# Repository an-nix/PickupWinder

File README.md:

# PickupWinder — Raspberry Pi + ESP32 Automated Winding Controller

An automated guitar pickup winding system driven by a Raspberry Pi host and an ESP32 real-time motion controller. The RPi handles planning, geometry, and user-facing APIs. The ESP32 drives the stepper motors in hard real-time using the RMT peripheral.

---

## Table of contents

1. [What it does](#what-it-does)
2. [Hardware overview](#hardware-overview)
3. [Repository layout](#repository-layout)
4. [Key concepts](#key-concepts)
5. [Getting started](#getting-started)
6. [Configuration reference](#configuration-reference)
7. [Winding a pickup — step by step](#winding-a-pickup--step-by-step)
8. [JSON-RPC API quick reference](#json-rpc-api-quick-reference)
9. [Further reading](#further-reading)

---

## What it does

PickupWinder automates or semi-automates the process of winding guitar pickup coils.
The machine moves two stepper axes in synchrony:

- **Spindle axis (axis 0)**: rotates the pickup bobbin.
- **Lateral axis (axis 1)**: moves the wire guide back and forth across the winding window.

The host computes exactly how far the guide must travel for each spindle revolution
(the *layer pitch*) and streams that motion to the ESP32 as pre-computed multi-axis
segment blocks. The ESP32 expands those segments into step pulses and streams them
to the motor drivers via the RMT peripheral.

Two winding modes are supported:

| Mode | Class | Description |
|------|-------|-------------|
| **Classic** | `WindingEngine` | Fixed program: N turns, fixed window, optional scatter, one shot. |
| **Adaptive** | `AdaptiveWindingService` | Live session: target RPM, window, and pitch can be changed while running. Progress is tracked in turns. |

---

## Hardware overview

```
  Raspberry Pi                     ESP32
  ─────────────────────────────────────────────────────
  spidev (master, mode 1) ──SPI──> slave (mode 1, DMA)
  GPIO poll / sysfs       <──────  GPIO17 READY output
  (optional shutdown)     <──────  GPIO16 RPI_SHUTDOWN_REQ

  ESP32 ──STEP/DIR──> Spindle stepper driver ──> Bobbin
  ESP32 ──STEP/DIR──> Lateral stepper driver ──> Wire guide
  ESP32 <── HX711 (tension load cell)
  ESP32 <── Rotary encoder (optional spindle feedback)
  ESP32 <── Lateral endstop (2-contact homing sensor)
```

- SPI bus: fixed 512-byte frames, mode 1 (CPOL=0, CPHA=1), CRC16-CCITT-FALSE.
- The ESP32 signals that it is ready to accept a new frame by asserting GPIO17 (active high by default).
- Do **not** drive GPIO12 high at boot — it straps the ESP32 flash voltage.

---

## Repository layout

```
src/
  windy/              Python host application
    winding_main.py   Process entry point and signal handling
    app/runtime.py    Runtime composition (wires all components together)
    core/
      config.py       AppConfiguration dataclass — all machine parameters
      engine.py       WindingEngine — classic program execution
      lateral.py      Lateral homing, soft-limit enforcement
      command_service.py  Motion command building and queuing
      coordinator.py  Centralized stop/fault coordination
      shared_state.py Thread-safe state shared between engine and RPC
      events.py       EventBus (EventKind enum + async dispatch)
      status.py       Snapshot builders for RPC status responses
    motion/
      move_queue.py   Move serialization and firmware flush coordination
      move.py         Move types: RampMove, HomingMove, CompositeMove
      move_builders.py  Factories for jog, homing, wound moves
      segment_generator.py   Host-side segment generation utilities
      multi_axis_segment_generator.py  General multi-axis move iterator
      spindle_kinematics.py  Bobbin turn profile over time (trapezoidal)
      trapezoidal_profile.py Trapezoidal speed ramp
      ramp_config.py  Low-level ramp parameters
      axis_state.py   Per-axis runtime state (position, home flag, limits)
    transport/
      messages.py     Python protocol mirror + wrap-aware sequence helpers
      spi_transport.py  SPI framing, polling, ACK confirmation
      streamer.py     MultiAxisRampStreamer — buffered segment streaming
      mock_spi_transport.py  In-process mock for testing
    winding/
      program.py      WindingProgram — persistent winding recipe
      session.py      SessionParams — transient execution context
      service.py      AdaptiveWindingService — live winding session
      adaptive.py     AdaptiveWindingRuntime — chunk planner
      wound_move.py   WoundMove / SynchronizedMove — electronic gearing move
      winding_pattern.py  Triangular traverse wave from spindle turns
      scatter_engine.py   Non-harmonic scatter with edge damping
      synchronized_segment_generator.py  Multi-axis segment iterator for winding
      program_store.py  Persistent program library (JSON files on disk)
      program.py      WindingProgram dataclass
    jsonrpc/
      rpc_server.py   Unix-socket JSON-RPC 2.0 server
      winding_handler.py  Facade that wires the four domain handlers
      execution_handler.py  winding.submit_program, wound_run, stop, status
      machine_handler.py   winding.jog, home_lateral, endstop, fault_clear
      session_handler.py   winding.start_session, pause, resume, update
      program_handler.py   program.list/get/save/update/load/delete
      handlers.py     Base RpcHandler dispatcher
      protocol.py     JSON-RPC 2.0 framing and error types

  esp32/              ESP-IDF firmware
    src/
      main.cpp        Pin map and app_main()
      messages.h      Packed protocol structs (must stay in sync with messages.py)
      comm/
        comm_interface.cpp    SPI slave task, CRC, dedup, dispatch
        comm_request_dispatcher.cpp  Route requests to handlers
        comm_status_builder.cpp     Build StatusPayload responses
      motion/
        motion_planner.cpp    Monotonic motion queue, flush handling
        multi_axis_executor.cpp  Segment expansion, ring fill, kick-start
        stepper_queue.cpp     Step ring management
        stepper_driver.cpp    RMT streaming, coast mode, underrun handling
      sensors/
        sensor_task.cpp       HX711, potentiometer, encoder acquisition
        endstop.cpp           2-contact lateral endstop handling

  wendy/              Lightweight HTTP bridge (Python)
    server.py         HTTP server → JSON-RPC forwarding
    handlers.py       REST endpoint handlers
    rpc.py            JSON-RPC client to Windy socket

data/                 Runtime data (created at startup if absent)
  config.json         Machine configuration (see Configuration reference)
  programs/           Saved winding programs (JSON files)

doc/                  Technical documentation
  architecture.md     Full system architecture
  spi_protocol.md     SPI frame format and ACK semantics
  sequencing.md       Sequence spaces, wrap-around safety, dedup rules
  stepper_engine.md   ESP32 RMT pipeline and ring buffer design
```

---

## Key concepts

### Program (`WindingProgram`)

A persistent recipe that describes **what** to wind, independent of the machine it runs on.
Saved to `data/programs/<id>.json`. Key fields:

| Field | Description |
|-------|-------------|
| `target_turns` | Total spindle turns to wind. Layer count is computed automatically. |
| `layer_pitch_mm` | Lateral advance per spindle revolution (mm). Equals wire diameter for tight winding. |
| `wire_diameter_mm` | Wire gauge in mm (informational, used in estimates). |
| `bobbin_width_mm` | Interior winding window width (flatwork to flatwork, mm). |
| `flatwork_thickness_mm` | Bobbin cheek/flatwork thickness (mm). Used to compute the start position. |
| `scatter_amplitude_mm` | Peak-to-peak scatter offset on the traverse (mm). `0` = no scatter. |
| `window_start_clearance_mm` | Per-program override for the safety gap at the winding start. `null` → use config default. |
| `window_end_clearance_mm` | Per-program override for the safety reduction at the far end. `null` → use config default. |

`num_layers` is **not stored** — it is derived:
```python
num_layers = ceil(target_turns / (2 * bobbin_width_mm * turns_per_mm))
# where turns_per_mm = 1 / layer_pitch_mm
```

### Session (`SessionParams`)

Transient execution context for one run. Not persisted. Key fields:

| Field | Description |
|-------|-------------|
| `spindle_rpm` | Target spindle speed. |
| `total_turns` | Optional override for `program.target_turns`. |
| `window_low_mm` / `window_high_mm` | Optional explicit window bounds override. |
| `chunk_time_s` | Adaptive planner chunk duration (default 0.25 s). |

### Configuration (`AppConfiguration`)

Machine-level parameters stored in `data/config.json`. They describe the hardware, not the pickup.
See [Configuration reference](#configuration-reference) for the full list.

### Winding window geometry

The lateral axis start position is built up from a chain of machine and program parameters:

```
window_low  = lateral_soft_limit_min_mm    ← plateau / homing reference edge
            + lateral_axis_offset_mm       ← machine fine-tuning (usually 0.0)
            + flatwork_thickness_mm        ← bobbin cheek thickness (per program)
            + window_start_clearance_mm    ← safety gap before first wire turn

window_high = window_low + bobbin_width_mm - window_end_clearance_mm
```

`window_start_clearance_mm` and `window_end_clearance_mm` have machine-level defaults
in `AppConfiguration` (`0.3 mm` and `0.0 mm`) that can be overridden per program.

### Electronic gearing model

The spindle and lateral axes are never driven independently during winding.
For every spindle revolution the guide must advance exactly `layer_pitch_mm`.

`WindingPattern.guide_pos_mm(spindle_turns)` implements the triangular wave:

```python
def guide_pos_mm(self, spindle_turns: float) -> float:
    total_dist = spindle_turns / self.turns_per_mm
    cycle_length = 2.0 * self.bobbin_width_mm
    mod_dist = total_dist % cycle_length
    return mod_dist if mod_dist <= self.bobbin_width_mm else cycle_length - mod_dist
```

`ScatterEngine` adds a small, non-repeating offset to break inter-layer resonance.

---

## Getting started

### 1. Build and flash ESP32 firmware

```bash
cd src/esp32
pio run -t upload          # PlatformIO
# or: idf.py build flash   # ESP-IDF native
```

### 2. Create a configuration file

Create `~/data/config.json` (or let the application create it with defaults on first run).
Minimal configuration for a typical build:

```json
{
  "spi_device": "/dev/spidev0.0",
  "spi_speed_hz": 4000000,
  "lateral_soft_limit_min_mm": 30.0,
  "lateral_axis_length_mm": 130.0,
  "window_start_clearance_mm": 0.3,
  "window_end_clearance_mm": 0.0
}
```

### 3. Start the host application

```bash
cd src/windy
python3 winding_main.py
```

The application opens the JSON-RPC socket at `/tmp/winding.sock` and starts the
winding engine and SPI transport. The lateral axis must be homed before any winding
can begin (this happens automatically when a program is submitted if `home_before_start`
is `true` in the config).

### 4. Create and run a winding program

```bash
# Save a program
echo '{"method":"program.save","params":{"name":"Strat bridge","target_turns":8000,
  "layer_pitch_mm":0.065,"wire_diameter_mm":0.063,"bobbin_width_mm":13.2,
  "flatwork_thickness_mm":3.2},"id":1,"jsonrpc":"2.0"}' | nc -U /tmp/winding.sock

# Run it (returns immediately; winding happens in background)
echo '{"method":"winding.submit_program","params":{"spindle_rpm":500,
  "program_id":"<id from above>"},"id":2,"jsonrpc":"2.0"}' | nc -U /tmp/winding.sock

# Poll status
echo '{"method":"winding.status","params":null,"id":3,"jsonrpc":"2.0"}' | nc -U /tmp/winding.sock
```

A sample program is included at `data/programs/programme-type-single-coil-42awg.json`.

---

## Configuration reference

All fields live in `src/windy/core/config.py` as the `AppConfiguration` dataclass.
Default values are shown. Override any field in `data/config.json`.

### SPI transport

| Field | Default | Description |
|-------|---------|-------------|
| `spi_device` | `"/dev/spidev0.0"` | Linux SPI device path. |
| `spi_speed_hz` | `4000000` | SPI clock frequency in Hz. |
| `spi_ready_gpio_chip` | `"/dev/gpiochip0"` | GPIO chip for the READY sideband. |
| `spi_ready_gpio_line` | `17` | GPIO line for the READY signal (GPIO17). |

### Spindle axis (axis 0)

| Field | Default | Description |
|-------|---------|-------------|
| `spindle_steps_per_revolution` | `200` | Full-step count for the spindle motor. |
| `spindle_microstepping` | `32` | Microstepping divisor. |
| `spindle_max_speed_rpm` | `1750` | Speed cap. |
| `spindle_accel_s` | `0.5` | Ramp-up time per layer (s). |
| `spindle_decel_s` | `0.5` | Ramp-down time per layer (s). |

### Lateral axis (axis 1)

| Field | Default | Description |
|-------|---------|-------------|
| `lateral_steps_per_revolution` | `96` | Full-step count for the lateral motor. |
| `lateral_microstepping` | `32` | Microstepping divisor. |
| `lateral_traverse_pitch_mm` | `1.0` | Lead screw pitch in mm/rev. |
| `lateral_soft_limit_min_mm` | `30.0` | Hard reference: plateau/homing edge in machine coordinates (mm). |
| `lateral_soft_limit_max_mm` | `null` | Optional upper travel limit (mm). |
| `lateral_axis_length_mm` | `130` | Physical travel; sizes the homing approach move. |
| `lateral_axis_offset_mm` | `0.0` | Machine fine-tuning offset added to `soft_limit_min_mm`. |
| `lateral_target_speed` | `120.0` | Speed for post-homing and start-position moves (RPM). |

### Winding window defaults

| Field | Default | Description |
|-------|---------|-------------|
| `window_start_clearance_mm` | `0.3` | Safety gap at the start of the winding window. Overridable per program. |
| `window_end_clearance_mm` | `0.0` | Safety reduction at the far end. Overridable per program. |

### Homing

| Field | Default | Description |
|-------|---------|-------------|
| `home_before_start` | `true` | Automatically home before executing a program. |
| `lateral_homing_approach_rpm` | `120.0` | Fast approach speed. |
| `lateral_homing_search_rpm` | `20.0` | Slow creep speed for precise trigger. |
| `lateral_homing_backoff_steps` | `6144` | Steps to back away from endstop before slow search. |

---

## Winding a pickup — step by step

This is the typical operator workflow:

1. **Load a saved program** (`program.load` or inline payload in `winding.submit_program`).
2. **Submit the program** with a target RPM via `winding.submit_program`.
3. The engine transitions `IDLE → HOMING → RUNNING`.
4. After homing, the lateral axis moves to `window_low`:
   ```
   window_low = soft_limit_min + axis_offset + flatwork_thickness + start_clearance
   ```
5. For each of `num_layers` passes the engine enqueues one `WoundMove` (spindle + lateral in sync).
6. On completion the engine returns to `IDLE` and publishes a `PROGRAM_COMPLETED` event.

For a live adjustable session, use `winding.start_session` with a `SessionParams` payload.
The adaptive planner breaks the full run into short chunks (~250 ms) so RPM, window, and
pitch ratio can be changed between chunks without stopping.

---

## JSON-RPC API quick reference

The socket is at `/tmp/winding.sock` (configurable via `rpc_socket_path`).
All calls follow JSON-RPC 2.0. Parameters are always a single object (`{}`).

### System

| Method | Description |
|--------|-------------|
| `winder.ping` | Health check. Returns `{"pong": true}`. |
| `winder.status` | Full runtime snapshot (engine state, layer progress, fault message). |
| `winder.config` | Returns the active `AppConfiguration` as JSON. |
| `winder.shutdown` | Graceful process stop. |

### Programs

| Method | Key params | Description |
|--------|-----------|-------------|
| `program.list` | — | List all saved programs. |
| `program.get` | `program_id` | Get one program by ID. |
| `program.save` | program fields | Create a new program. Returns the assigned `program_id`. |
| `program.update` | `program_id` + fields | Update fields; bumps `revision`. |
| `program.load` | `program_id` | Mark a program as loaded (does not start winding). |
| `program.delete` | `program_id` | Delete a saved program. |

### Winding execution

| Method | Key params | Description |
|--------|-----------|-------------|
| `winding.submit_program` | `spindle_rpm`, optional `program_id` or inline fields | Queue a classic winding run. |
| `winding.wound_run` | `spindle_rpm`, `bobbin_width_mm`, `layer_pitch_mm`, `target_turns` | One-shot run without saving a program. |
| `winding.status` | — | Current engine state, layer index, turns wound. |
| `winding.stop` | — | Request a controlled stop. |

### Live session

| Method | Key params | Description |
|--------|-----------|-------------|
| `winding.start_session` | `spindle_rpm`, optional window/pitch/turns | Start an adaptive session. |
| `winding.update_session` | `spindle_rpm`, `window_low_mm`, `window_high_mm` | Change parameters mid-session. |
| `winding.pause` | — | Pause after current chunk. |
| `winding.resume_session` | — | Resume a paused session. |
| `winding.session_status` | — | Turns completed, RPM, guide position, window. |

### Machine control

| Method | Key params | Description |
|--------|-----------|-------------|
| `winding.home_lateral` | — | Start a homing cycle. |
| `winding.jog` | `axis_id`, `steps`, `rpm`, `reverse` | Single-axis jog move. |
| `winding.move_lateral_mm` | `position_mm`, `rpm` | Move lateral to absolute position. |
| `winding.set_axis_offset` | `offset_mm` | Update `lateral_axis_offset_mm` live. |
| `winding.clear_fault` | — | Clear fault state to return to IDLE. |
| `winding.arm_endstop` | `axis_id` | Arm the endstop for homing. |
| `winding.disarm_endstop` | `axis_id` | Disarm the endstop. |

---

## Further reading

| Document | Contents |
|----------|----------|
| [doc/architecture.md](doc/architecture.md) | Full software architecture, runtime flow, state machine, wiring details. |
| [doc/spi_protocol.md](doc/spi_protocol.md) | SPI frame format, message types, ACK pipelining, adding new messages. |
| [doc/sequencing.md](doc/sequencing.md) | Three sequence spaces, wrap-around safety, deduplication layers. |
| [doc/stepper_engine.md](doc/stepper_engine.md) | ESP32 RMT pipeline, ring buffer design, coast mode, key constants. |

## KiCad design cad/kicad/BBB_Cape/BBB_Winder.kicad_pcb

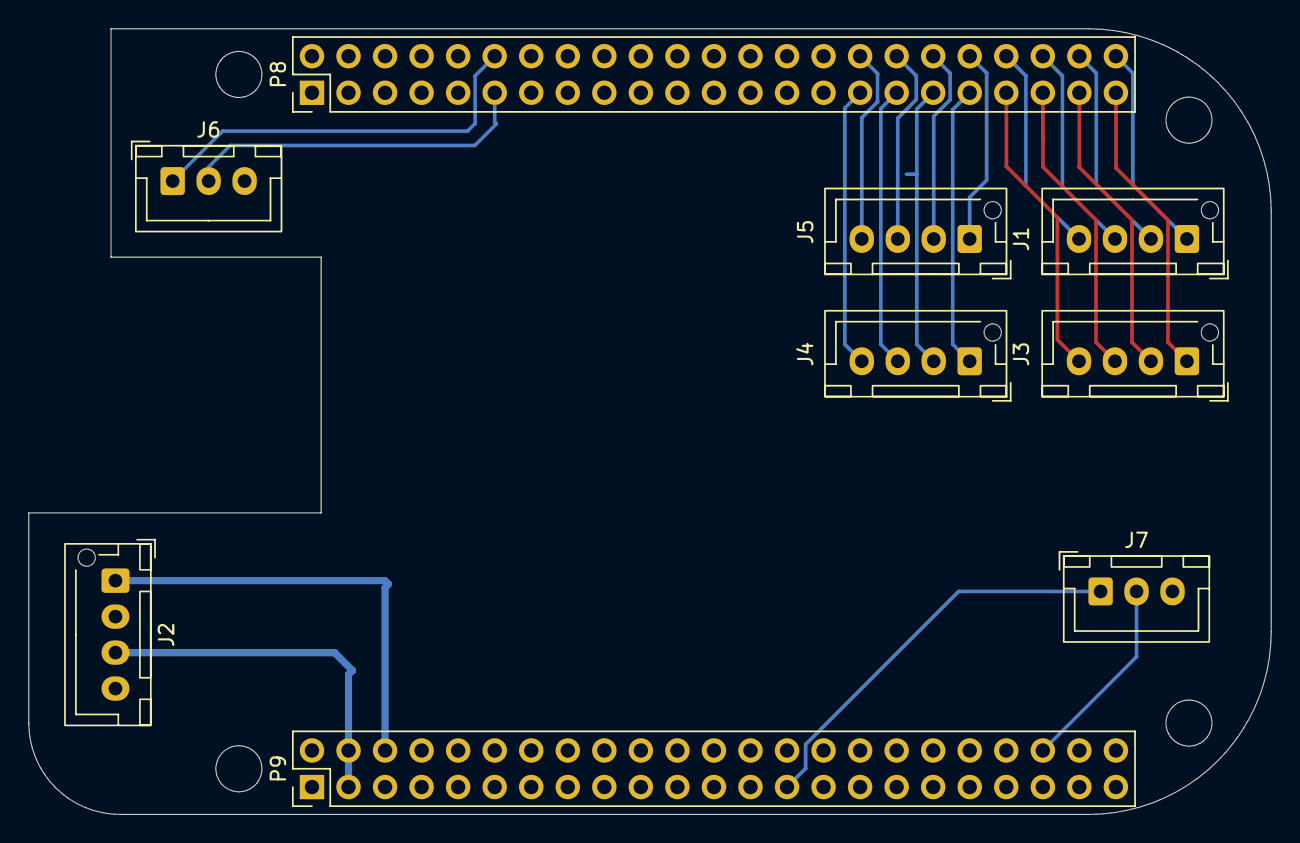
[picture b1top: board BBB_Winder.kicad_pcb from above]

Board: 2 copper layers, 86.4 x 54.6 mm, 13 parts (0 on the bottom side), 24 nets.

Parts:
J1: 0..3; JST_XH_B4B-XH-AM_1x04_P2.50mm_Vertical
J2: Power Header; JST_XH_B4B-XH-AM_1x04_P2.50mm_Vertical
J3: 4..7; JST_XH_B4B-XH-AM_1x04_P2.50mm_Vertical
J4: 12..15; JST_XH_B4B-XH-AM_1x04_P2.50mm_Vertical
J5: 8..11; JST_XH_B4B-XH-AM_1x04_P2.50mm_Vertical
J6: Encoder_1; JST_XH_B3B-XH-A_1x03_P2.50mm_Vertical
J7: Encoder_0; JST_XH_B3B-XH-A_1x03_P2.50mm_Vertical
MH1, MH2, MH3, MH4: MountingHole_3.2mm_M3_DIN965
P8, P9: BeagleBone_Black_Header; PinHeader_2x23_P2.54mm_Vertical

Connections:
+3V3: J2.3, P9.3, P9.4
+5V: J2.1, P9.5, P9.6
/GPIO7: J7.2, P9.42
/GPIO44: J6.1, P8.12
/GPIO125: J7.1, P9.27
/LCD.DATA1: J1.1, P8.46
/LCD.DATA3: J1.2, P8.44
/LCD.DATA5: J1.3, P8.42
/LCD.DATA7: J1.4, P8.40
/LCD.DATA9: J5.1, P8.38
/LCD.DATA10: J5.2, P8.36
/LCD.DATA11: J5.3, P8.34
/LCD.DATA15: J5.4, P8.32
GNDD: J2.2, J2.4, P8.1, P8.2, P9.1, P9.2, P9.43, P9.44, P9.45, P9.46
unnamed: J3.1, P8.45
unnamed: J3.2, P8.43
unnamed: J3.3, P8.41
unnamed: J3.4, P8.39
unnamed: J4.1, P8.37
unnamed: J4.2, P8.35
unnamed: J4.3, P8.33
unnamed: J4.4, P8.31
unnamed: J6.2, P8.11
VBUS: P9.7, P9.8

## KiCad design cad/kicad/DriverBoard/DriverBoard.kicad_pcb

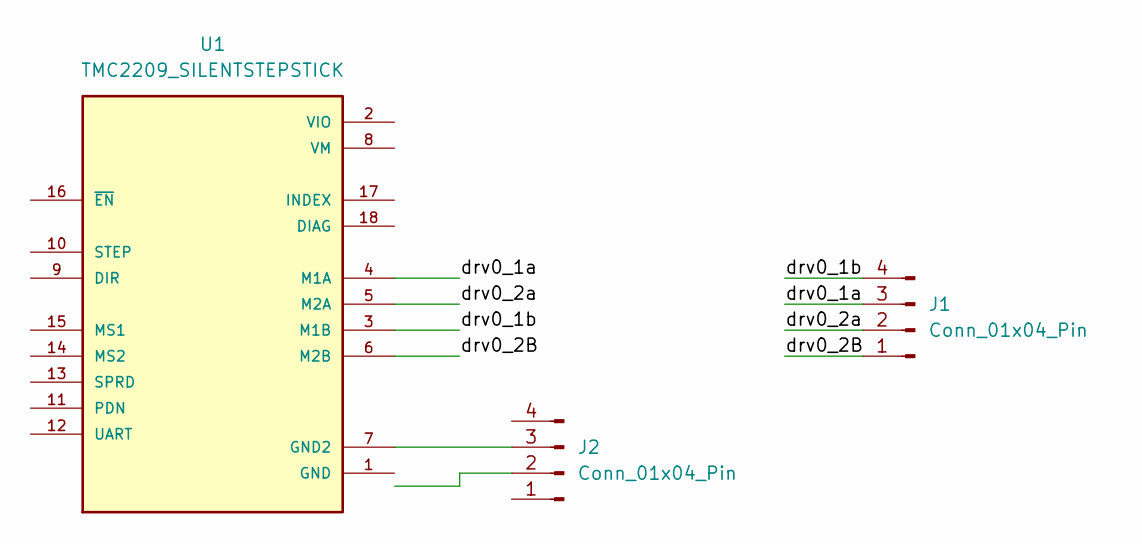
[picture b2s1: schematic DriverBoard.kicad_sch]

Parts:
J1, J2: Conn_01x04_Pin; JST_XH_B4B-XH-AM_1x04_P2.50mm_Vertical
U1: TMC2209_SILENTSTEPSTICK; MODULE_TMC2209_SILENTSTEPSTICK; PARTREV 1.20

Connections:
/drv0_1a: J1.3, U1.4 (M1A)
/drv0_1b: J1.4, U1.3 (M1B)
/drv0_2B: J1.1, U1.6 (M2B)
/drv0_2a: J1.2, U1.5 (M2A)
unnamed: J2.3 (Pin_3_3), U1.7 (GND2)

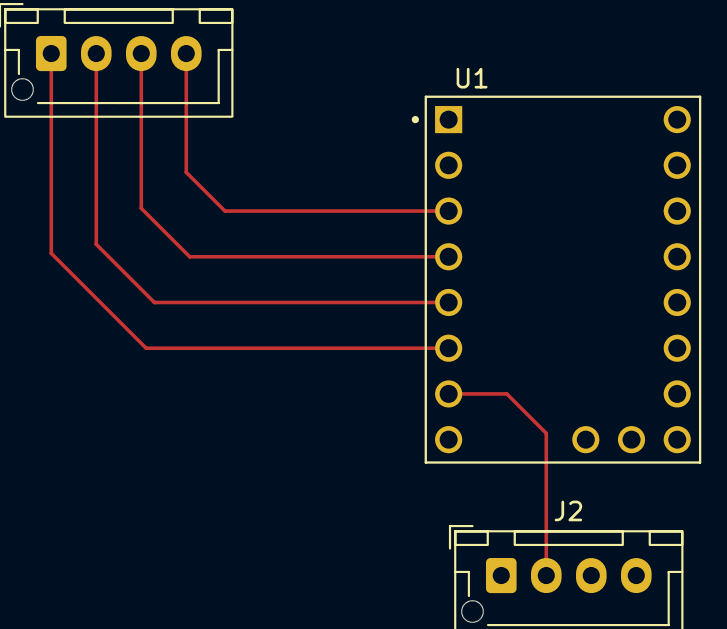
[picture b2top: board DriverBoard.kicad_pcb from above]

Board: 2 copper layers, 3 parts (0 on the bottom side), 5 nets.

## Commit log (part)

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2026-03-01 microsteps 32
2026-03-01 target reached
2026-03-01 freerun
2026-03-01 led flash at restart fix
2026-03-03 fix jerk
2026-03-05 add low turn
2026-03-08 lateral move
2026-03-08 moed normal
2026-03-09 rodage lateral
2026-03-09 lateral test
2026-03-10 bobinage
2026-03-11 femove rix
2026-03-11 fix stop overrun
2026-03-11 verify steps
2026-03-12 remove test
2026-03-14 stop on stop
2026-03-16 renversement opposé
2026-03-22 ui refactor
2026-03-26 Comment + Rewind
2026-03-27 clean
2026-03-27 Unlock RPM & Pause fix
2026-03-27 refactor
2026-03-27 freertos
2026-03-27 freertos & cleanup
2026-03-27 now fix
2026-03-27 remove remaining file
2026-03-27 fix start mode
2026-03-27 footswitch
2026-03-28 UI: trim nudge buttons use arrows; fix command buffer length plus logging
2026-03-28 Secure wifi credentials via Secrets.h and ignore it in git
2026-03-28 Document secure Wi-Fi credentials mechanism in README
2026-03-28 Replace default Wi-Fi values with placeholders
2026-03-28 Allow CI Wi-Fi config via build defines and doc in README
2026-03-28 Extract Wi-Fi credentials logic to WifiConfig.h
2026-03-28 Ensure WifiConfig include is in secure-wifi-config
2026-03-28 double wifi config
2026-03-28 Revise README for full documentation and CI Wi-Fi instructions
2026-03-28 Add pinout diagram section to README
2026-03-28 README
2026-03-28 Document pot/footswitch/motor inversion variables in README
2026-03-28 wifi: centralize config in Config.h; add WifiManager; decouple WebInterface; update README; remove Secrets.h
2026-03-28 session: require explicit UI Start when IDLE; ignore pot/footswitch baseline events
2026-03-31 Remove winding styles; keep straight-only; use float TPP; update telemetry and planner
2026-03-31 Remove burst mode: eliminate burst fields, logic, UI and client handling
2026-03-31 fix(wifi): robust NVS init and credential branch logging; no String allocations
2026-03-31 Fix CI: sync WifiManager/NvsCompat/WebInterface API and add NVS compatibility layer
2026-03-31 gitinore
2026-03-31 untracked files on dev/wifi-nvs-fix: 019eb2d fix(wifi): robust NVS init and credential branch logging; no String allocations
2026-03-31 Refactor to C-string command path; remove dynamic String usage; recipe JSON to C-buffer; local build OK
2026-04-01 chore: final audit fixes compensation, lateral reversal, geometry, tests, cleanup
2026-04-01 fix: add LAT_REVERSAL_SLOWDOWN constant and remove duplicate WinderApp.cpp; esp32dev build clean
2026-04-01 refactor: unify command identifiers via CommandId across registry, session, and winder app command handlers
2026-04-01 enhance: add CommandRegistry::findById and command-id dispatch tracing in WinderApp
2026-04-02 beagle migration
2026-04-03 pru: detect toolchain in $HOME/x-tools; fix PRU build & deploy targets
2026-04-03 build artifcat gitignore
2026-04-03 pru: expand README with detailed entry points, IPC layout, commands, GPIOs, build and deploy notes
2026-04-03 tools(pru): add list_pru_pins.sh to enumerate header pins using config-pin
2026-04-03 docs(pru): include detected PRU-capable header pins in README and copilot-instructions
2026-04-04 pru: dual-stepper PRU1 firmware on P8_41-P8_46
    Add pru1_dual_stepper/main.c: single PRU1 firmware driving both
    SPINDLE and LATERAL axes simultaneously on P8 header (LCD_DATA pins).
    GPIO mapping (PRU1 R30):
    R30[1] P8_46 SPINDLE_STEP R30[3] P8_44 SPINDLE_DIR R30[5] P8_42 SPINDLE_EN
    R30[0] P8_45 LATERAL_STEP R30[2] P8_43 LATERAL_DIR R30[4] P8_41 LATERAL_EN
    Key changes:
2026-04-04 docs(pru): add PRU_DEPLOY.md manual deploy guide
2026-04-04 docs: add PRU/BeagleBone P8 pin mapping to README
2026-04-04 docs(pru): handle missing config-pin / bb-cape-overlays; add alternatives (dtbo, install, pull-ups)
2026-04-05 a lot of things
2026-04-06 working eqep
2026-04-06 4eqep dts
2026-04-06 4eqeps
2026-04-06 move eqeqp from test to resources
2026-04-06 host io
2026-04-06 switch to eqep2b
2026-04-06 eqep2
2026-04-06 cirrect adress and doc
2026-04-06 add gpio P9_23
2026-04-06 add copilot instructions
2026-04-07 merged dts by type
2026-04-07 documentation
2026-04-07 cleanup
2026-04-07 install script
2026-04-07 cross compilation
2026-04-07 adapt compiler name
2026-04-08 docker cross-compile
2026-04-08 backup: move local docker to docker-local-backup before adding submodule
2026-04-08 chore(submodule): update bbb-crosscompile to include local docker files
2026-04-08 chore(submodule): add .gitmodules entry for tools/bbb-crosscompile
2026-04-08 submodule
2026-04-08 chore(submodule): update bbb-crosscompile submodule to include ARM cross-compiler packages
2026-04-08 chore: add tools/docker-build.sh helper to run build in container as host user
2026-04-08 chore: add top-level docker-build.sh one-click wrapper
2026-04-08 chore: add Makefile target 'docker-build' to run docker-based build
2026-04-08 fix: use container-owned chown for build/ ownership fixing
2026-04-08 fix: run build and chown in a single docker container
2026-04-08 feat: support optional make targets in docker-build script and Makefile
2026-04-08 fix: run docker build as current host user to preserve ownership
2026-04-08 chore: update bbb-crosscompile submodule SHA after toolchain runtime fix
2026-04-08 chore: remove obsolete tools/docker-build.sh helper
2026-04-08 feat: professional Docker build pipeline + GitHub Actions CI
    docker-build.sh:
    - Rewrite with proper flag parsing (--image, --log, --jobs, --help)
    - Single docker run invocation (remove duplicate if/else for empty targets)
    - Correct exit-code propagation through tee pipe (set +e / PIPESTATUS)
    - Colour output, build timing, pre-flight Docker daemon check
    - ':z' SELinux label on volume mount
2026-04-08 ci: toolchain-image — manual trigger only (remove auto push)
2026-04-08 ci: switch registry from GHCR to Docker Hub
    - build.yml: IMAGE=antnic/bbb-crosscompile:debian12, login via
    DOCKERHUB_USERNAME/DOCKERHUB_TOKEN secrets, drop packages:read permission
    - toolchain-image.yml: push to antnic/bbb-crosscompile, login via
    DOCKERHUB_USERNAME/DOCKERHUB_TOKEN, drop GHCR env vars and packages:write,
    update BuildKit cache refs to Docker Hub
2026-04-08 ci: remove toolchain-image workflow, drop Docker Hub login in build
    - toolchain-image.yml deleted (image built/pushed manually with make docker-image-push)
    - build.yml: remove login step (antnic/bbb-crosscompile is a public image)
2026-04-08 fix: bump bbb-crosscompile submodule (chmod PRU toolchain fix)
2026-04-08 fix: bump bbb-crosscompile (ct-ng silent build, show tail on error)
2026-04-08 feat: live ct-ng logs + host-side build log
    - Bump bbb-crosscompile submodule (ct-ng streams to stdout)
    - docker-image target: --progress=plain + tee build/docker-image-build.log
    so the full build log is saved on the host after make docker-image
2026-04-08 fix: add BUILDKIT_STEP_LOG_MAX_SIZE=-1 to remove 2MiB log cap
2026-04-08 fix: disable BuildKit for docker image builds to avoid 2MiB log clipping
    - Makefile docker-image: use DOCKER_BUILDKIT=0 (classic builder streams full ct-ng logs)
    - CI fallback docker build: also disable BuildKit
    - Remove stale reference to removed toolchain-image workflow
2026-04-08 fix: bump bbb-crosscompile (apt HTTPS + retries for signature errors)
2026-04-08 image
2026-04-09 review pinout
2026-04-09 fix(pru): add 'register' keyword to __R30/__R31 — writes were going to RAM not pins
    Without 'register', __asm__("r30") on a global creates a RAM symbol named r30.
    PRU appeared functional (step counts incremented) but no GPIO ever changed.
    Also fix:
    - DTS: MODE6→MODE5 on PRU0 output pins (MODE6=R31 input, MODE5=R30 output)
    - daemon: O_NONBLOCK + EAGAIN in broadcast() — blocking write() froze event loop
    - Makefile: add -Wno-volatile-register-var, test-static and test-gpio targets
2026-04-10 invert PRU0 & PRU1
2026-04-10 sync
2026-04-10 mode
2026-04-10 seq diagram
2026-04-11 pru + daemon + motor
2026-04-11 refactor: generic per-axis ramp architecture + PRU1 as dumb motor driver
    ARCHITECTURE CHANGES:
    - Ramp/acceleration is now generic per-axis (was spindle-specific)
    - PRU0 (orchestrator) manages ramp segments via ramp_tick() for BOTH axes
    - PRU1 (motor control) is truly dumb: detects ramp_arm → executes segment → reports seg_done
    - All intelligence (segment sequencing, homing, coordination) lives in PRU0
    IPC REDESIGN (pru_ipc.h):
2026-04-11 proto de rop
2026-04-12 accel fix
2026-04-12 pru1: reduce motor noise via shadow EN/DIR registers + unified STEP write
    Root causes identified:
    1. apply_enable/dir() called unconditionally every loop (~200 MHz).
    Each __R30 |= / &=~ call toggled EN and DIR at full PRU loop rate even
    when unchanged → HF noise on stepper driver inputs → audible buzz.
    2. Two separate read-modify-write instructions for SP_STEP and LAT_STEP
    left a brief glitch window between the two axis updates.
2026-04-12 pru/daemon/py: constant-time PRU1, PRU0 seg-advance, daemon homing FSM
    PRU1 (motor_control/main.c):
    - Pure constant-time pulse generator: LOOP_CYCLES_TARGET=650 busy-wait
    guarantees every iteration is exactly 650 IEP cycles → no rhythmic
    timing noise on STEP output (fixes high-speed grinding)
    - Removed: g_ramp_segs[], segment auto-advance, publish_telem(), TELEM_STRIDE
    - Added: inline telem writes (accel_count, step_count, position) every loop
2026-04-12 python
2026-04-12 remove kicad history
2026-04-12 python move
2026-04-12 python proto
2026-04-13 clean python
2026-04-13 proto
2026-04-14 directory structure
2026-04-14 compile test
2026-04-16 framework change
2026-04-16 running motor with demo
2026-04-16 dodo
2026-04-17 streamer
2026-04-17 log try2
2026-04-17 refact
2026-04-17 joming
2026-04-17 ok, underrun low speed
2026-04-17 working, sporadic underrun
2026-04-17 add homing test
2026-04-18 reverse
2026-04-18 motor always enable
2026-04-18 import correc
2026-04-18 json rpc
2026-04-18 pythontype
2026-04-19 firmware planner
2026-04-19 firmware
2026-04-19 acceleration a revoir
2026-04-19 host send logic
2026-04-19 lastExecutedSequence
2026-04-19 python refactor
2026-04-19 ai analyze v4
2026-04-19 ai analyze V5
2026-04-19 Refactor V8
2026-04-20 no stall, speed changes
2026-04-20 all sources
2026-04-20 sequnceur
2026-04-20 fix a9
2026-04-20 long run + log
2026-04-20 better
2026-04-20 ok 5min
2026-04-20 rmt reset
2026-04-20 lateral
2026-04-20 add linux concat script
2026-04-20 homing prot
2026-04-20 project cleanup
2026-04-20 remove obsolete file
2026-04-20 code cleanup
2026-04-20 wendy
2026-04-20 run_axis handler
2026-04-20 remove obsolete ramp
2026-04-20 remove ressources
2026-04-21 architectural refacto
2026-04-21 rypo
2026-04-22 homing + spi + ack on control only
2026-04-22 firmware endstop
2026-04-22 homing nok
2026-04-22 doc and prequeue test
2026-04-22 spi mode1
2026-04-22 mode1
2026-04-22 30s 1500
2026-04-23 last try
2026-04-23 ready pin
2026-04-24 split
2026-04-24 esp cleanup
2026-04-24 scripts
2026-04-24 fix homing
2026-04-24 fw ok
2026-04-24 better homing
2026-04-29 homing
2026-05-04 homing better
2026-05-04 homing working
2026-05-04 clear api
2026-05-05 homing ok
2026-05-05 fix axis reverse
2026-05-05 RMT frequency 80000
2026-05-05 add low speed
2026-05-05 clean doc
2026-05-05 Cleanup: suppression des shims de compatibilité obsolètes, suppression de la classe SessionPersistenceService orpheline, déplacement de segment_json vers diag, correction des imports et nettoyage des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
2026-05-06 refactor plan
2026-05-06 remove step-based legacy code
2026-05-06 remove mono-axis SEGMENT_BLOCK
2026-05-06 delete
2026-05-06 direction_mask
2026-05-07 docs(refactor): remove legacy STEP_BLOCK/SEGMENT_BLOCK mentions from core docs
2026-05-07 remove doc
2026-05-08 branch
2026-05-08 offset config
2026-05-08 offset
2026-05-09 remove build.yaml
2026-05-09 axis length for max homing mvt
2026-05-10 wendy program load/save
2026-05-10 homing xi
2026-05-21 next steps
2026-05-22 rename rpi to windy
